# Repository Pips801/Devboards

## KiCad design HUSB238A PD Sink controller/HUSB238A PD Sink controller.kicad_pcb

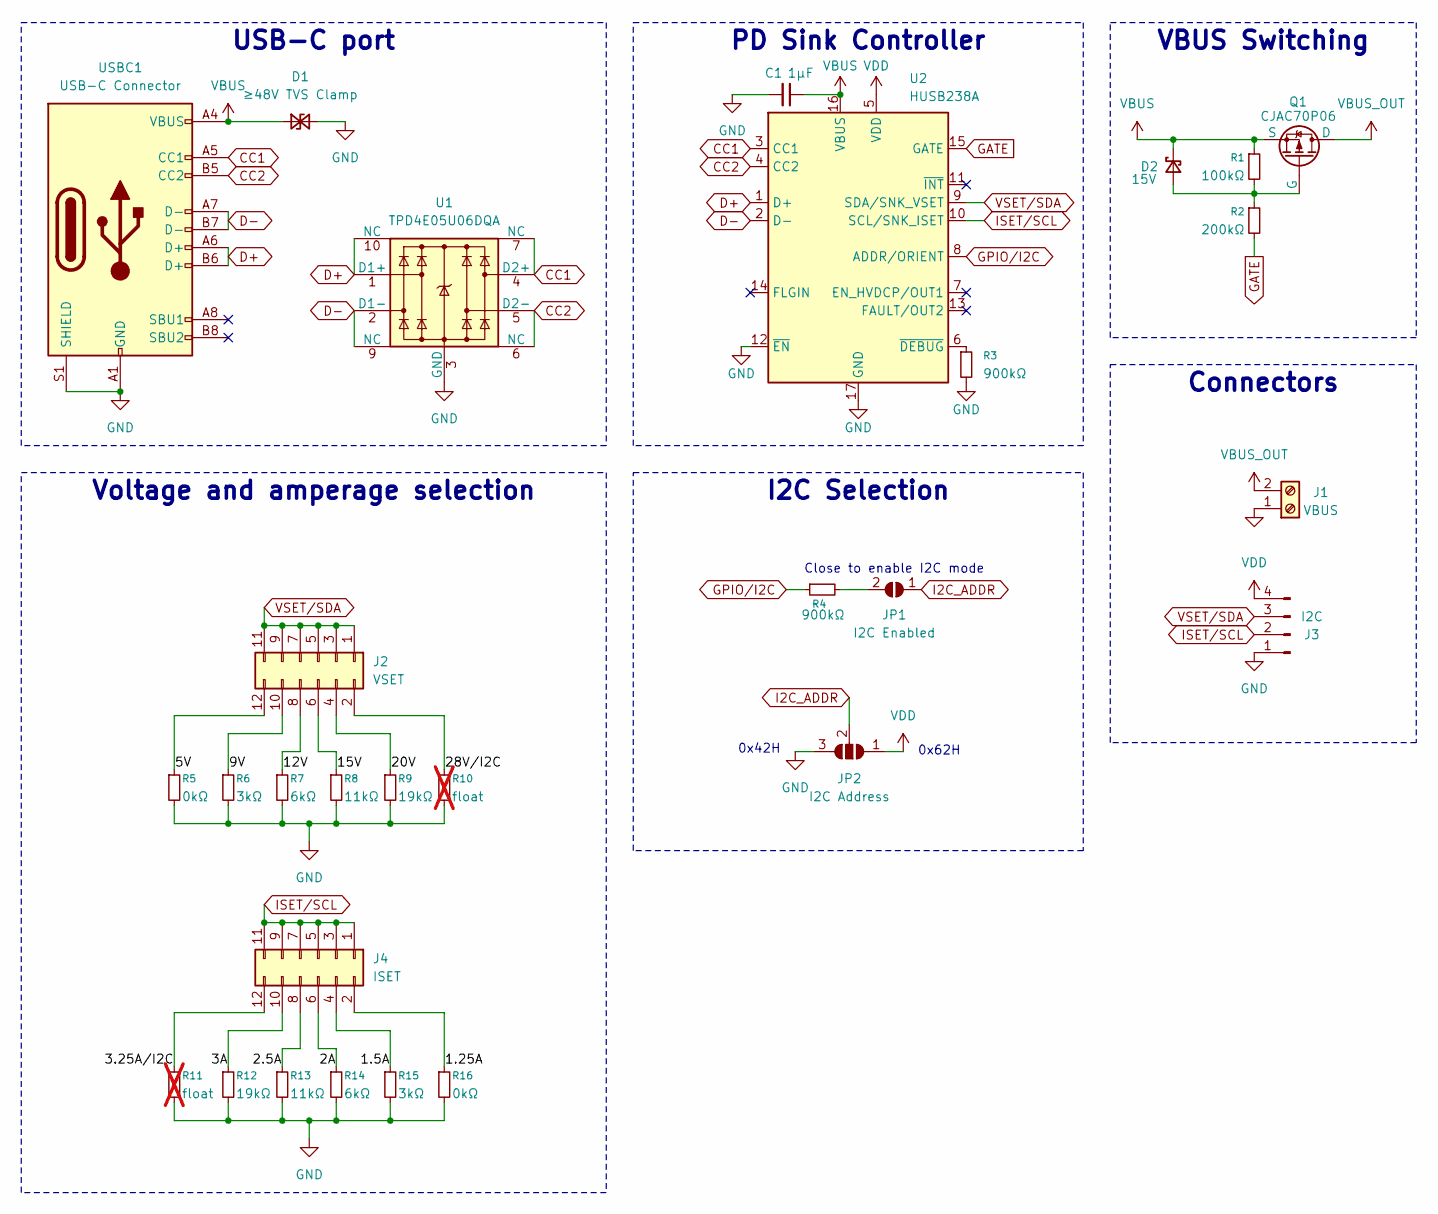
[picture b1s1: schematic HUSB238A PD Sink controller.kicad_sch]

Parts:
C1: 1μF; C_0603_1608Metric; LCSC Part # C15849
D1: ≥48V TVS Clamp; D_SOD-123F; LCSC Part # C5353371
D2: 15V; D_SOD-323; LCSC Part # C41410799
J1: VBUS; PinHeader_1x02_P2.54mm_Vertical
J2: VSET; PinHeader_2x06_P2.54mm_Vertical
J3: I2C; PinHeader_1x04_P2.54mm_Vertical
J4: ISET; PinHeader_2x06_P2.54mm_Vertical
JP1: I2C Enabled; SolderJumper-2_P1.3mm_Open_RoundedPad1.0x1.5mm
JP2: I2C Address; SolderJumper-3_P1.3mm_Open_RoundedPad1.0x1.5mm_NumberLabels
Q1: CJAC70P06; PQFN-8-EP_6x5mm_P1.27mm_Generic; LCSC Part # C2898279
R1: 100kΩ; R_0603_1608Metric; LCSC Part # C25803
R2: 200kΩ; R_0603_1608Metric; LCSC Part # C25811
R3, R4: 900kΩ; R_0603_1608Metric; LCSC Part # C22935
R5, R16: 0kΩ; R_1206_3216Metric_Pad1.30x1.75mm_HandSolder; LCSC Part # C17888
R6, R15: 3kΩ; R_1206_3216Metric_Pad1.30x1.75mm_HandSolder; LCSC Part # C18012
R7, R14: 6kΩ; R_1206_3216Metric_Pad1.30x1.75mm_HandSolder; LCSC Part # C229764
R8, R13: 11kΩ; R_1206_3216Metric_Pad1.30x1.75mm_HandSolder; LCSC Part # C43670
R9, R12: 19kΩ; R_1206_3216Metric_Pad1.30x1.75mm_HandSolder; LCSC Part # C74154
R10, R11: float; R_1206_3216Metric_Pad1.30x1.75mm_HandSolder; not fitted
U1: TPD4E05U06DQA; USON-10_2.5x1.0mm_P0.5mm; LCSC Part # C138714
U2: HUSB238A; WQFN-16-1EP_3x3mm_P0.5mm_EP1.75x1.75mm; LCSC Part # C24833806
USBC1: USB-C Connector; USB_C_Receptacle_HRO_TYPE-C-31-M-12; LCSC Part # C2931470

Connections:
/1.5A: J4.4, R15.1
/1.25A: J4.2, R16.1
/2.5A: J4.8, R13.1
/2A: J4.6, R14.1
/3.25A/I2C: J4.12, R11.1
/3A: J4.10, R12.1
/5V: J2.12, R5.1
/9V: J2.10, R6.1
/12V: J2.8, R7.1
/15V: J2.6, R8.1
/20V: J2.4, R9.1
/28V/I2C: J2.2, R10.1
CC1: U1.4 (D2+), U1.7 (NC), U2.3 (CC1), USBC1.A5 (CC1)
CC2: U1.5 (D2-), U1.6 (NC), U2.4 (CC2), USBC1.B5 (CC2)
D+: U1.1 (D1+), U1.10 (NC), U2.1 (D+), USBC1.A6 (D+), USBC1.B6 (D+)
D-: U1.2 (D1-), U1.9 (NC), U2.2 (D-), USBC1.A7 (D-), USBC1.B7 (D-)
GATE: R2.2, U2.15 (GATE)
GND: C1.2, D1.2 (A2), J1.1, J3.1, JP2.3, R3.2, R5.2, R6.2, R7.2, R8.2, R9.2, R10.2, R11.2, R12.2, R13.2, R14.2, R15.2, R16.2, U1.3 (GND), U1.8 (GND), U2.12 (~EN), U2.17 (GND), USBC1.A1 (GND), USBC1.A12 (GND), USBC1.B1 (GND), USBC1.B12 (GND), USBC1.S1 (SHIELD)
GPIO/I2C: R4.1, U2.8 (ADDR/ORIENT)
I2C_ADDR: JP1.1 (A), JP2.2 (ADDR)
ISET/SCL: J3.2, J4.1, J4.3, J4.5, J4.7, J4.9, J4.11, U2.10 (SCL/SNK_ISET)
unnamed: D2.2 (A), Q1.4 (G), R1.2, R2.1
unnamed: JP1.2 (B), R4.2
unnamed: R3.1, U2.6 (~DEBUG)
VBUS: C1.1, D1.1 (A1), D2.1 (K), Q1.1 (S), Q1.2 (S), Q1.3 (S), R1.1, U2.16 (VBUS), USBC1.A4 (VBUS), USBC1.A9 (VBUS), USBC1.B4 (VBUS), USBC1.B9 (VBUS)
VBUS_OUT: J1.2, Q1.5 (D), Q1.6 (D), Q1.7 (D), Q1.8 (D)
VDD: J3.4, JP2.1, U2.5 (VDD)
VSET/SDA: J2.1, J2.3, J2.5, J2.7, J2.9, J2.11, J3.3, U2.9 (SDA/SNK_VSET)

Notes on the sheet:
0x62H
0x42H
Close to enable I2C mode
I2C Selection
PD Sink Controller
Voltage and amperage selection
VBUS Switching
USB-C port
Connectors

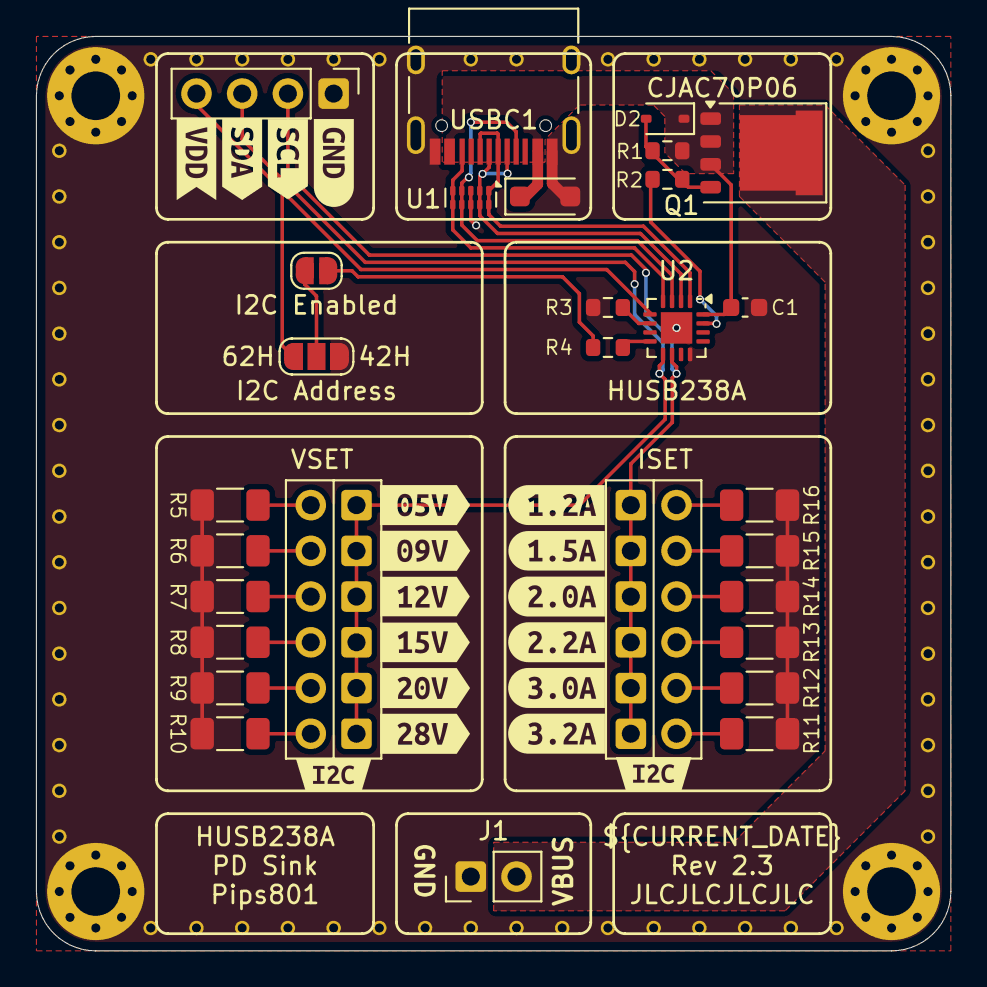
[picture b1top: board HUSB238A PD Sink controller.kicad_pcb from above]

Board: 2 copper layers, 50.8 x 50.8 mm, 47 parts (0 on the bottom side), 28 nets.

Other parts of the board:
kibuzzard-6951C990, kibuzzard-6951C990#2: G***; kibuzzard-6951C990
kibuzzard-6951CA75: G***; kibuzzard-6951CA75
kibuzzard-6951CAED: G***; kibuzzard-6951CAED
kibuzzard-6951CAFD: G***; kibuzzard-6951CAFD
kibuzzard-6951CB2B: G***; kibuzzard-6951CB2B
kibuzzard-6951CB4D: G***; kibuzzard-6951CB4D
kibuzzard-6951CB7E: G***; kibuzzard-6951CB7E
kibuzzard-6951CB42: G***; kibuzzard-6951CB42
kibuzzard-6951CEE5: G***; kibuzzard-6951CEE5
kibuzzard-6951CF0B: G***; kibuzzard-6951CF0B
kibuzzard-6951CF1D: G***; kibuzzard-6951CF1D
kibuzzard-6951CF4B: G***; kibuzzard-6951CF4B
kibuzzard-6951CF39: G***; kibuzzard-6951CF39
kibuzzard-6951D5A7: G***; kibuzzard-6951D5A7
kibuzzard-6951D5B1: G***; kibuzzard-6951D5B1
kibuzzard-6951D5BC: G***; kibuzzard-6951D5BC
kibuzzard-6951D5C7: G***; kibuzzard-6951D5C7

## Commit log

2025-12-17 PD sink controller devboard initial commit
2025-12-29 R2.3
2025-12-29 rev 2.3
2025-12-29 Fix resistor values
2025-12-29 add datasheet
2026-01-01 diodes
